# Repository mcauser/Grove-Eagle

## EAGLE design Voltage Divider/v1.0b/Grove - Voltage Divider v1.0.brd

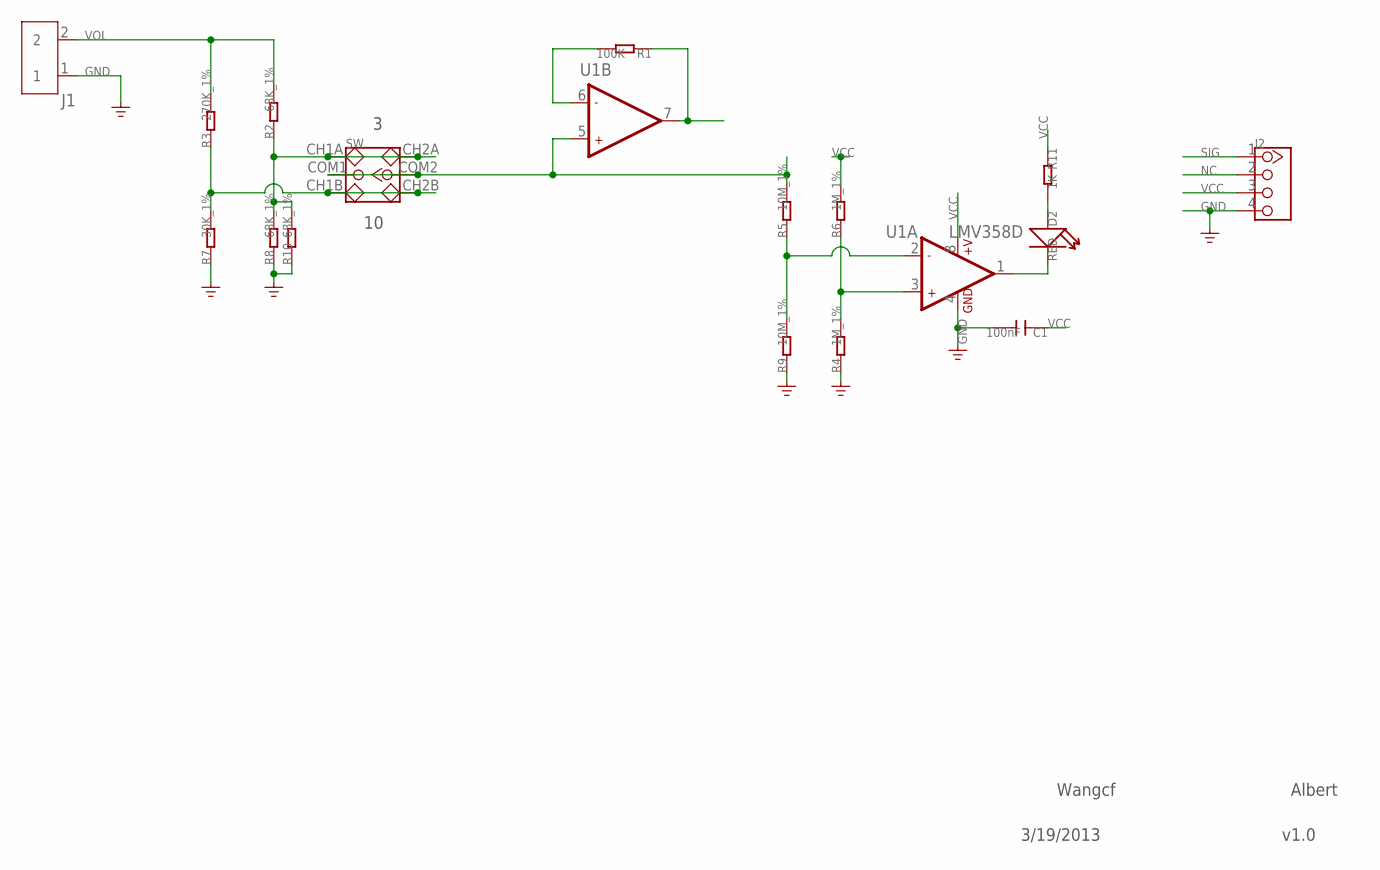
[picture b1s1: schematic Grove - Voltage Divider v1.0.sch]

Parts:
C1: 100nF; C0603
D2: RED; LED-0603
J1: SCREW-TERMINAL-2P'5.08'; 2P-5.08
J2: TWIG-4P-2.0-2.0; 4P-2.0
R1: 100K; R0603
R2, R8, R10: 68K_1%; R0603
R3: 270K_1%; R0603
R4, R6: 1M_1%; R0603
R5, R9: 10M_1%; R0603
R7: 30K_1%; R0603
R11: 1K; R0603
SW: SWITCH-2CH-6P'MS-22D18'; 6P-2CH-2.5-9.1X3.5X3.2H
U1: LMV358D; SO08

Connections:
GND: C1.2, J1.1, J2.4, R4.1, R7.1, R8.1, R9.1, R10.1, U1.4 (GND)
unnamed: D2.+, R11.2
unnamed: D2.-, U1.1 (OUT1)
unnamed: R5.1, R9.2, U1.2 (-IN1)
unnamed: R5.2, SW.COM1, SW.COM2, U1.5 (+IN2)
unnamed: R4.2, R6.1, U1.3 (+IN1)
unnamed: R1.2, U1.6 (-IN2)
NC: J2.2
SIG: J2.1, R1.1, U1.7 (OUT2)
VCC: C1.1, J2.3, R6.2, R11.1, U1.8 (+V)
VOL: J1.2, R2.2, R3.2
VOL1: R3.1, R7.2, SW.CH1B, SW.CH2B
VOL2: R2.1, R8.2, R10.2, SW.CH1A, SW.CH2A

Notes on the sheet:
Wangcf
Albert
3/19/2013
v1.0

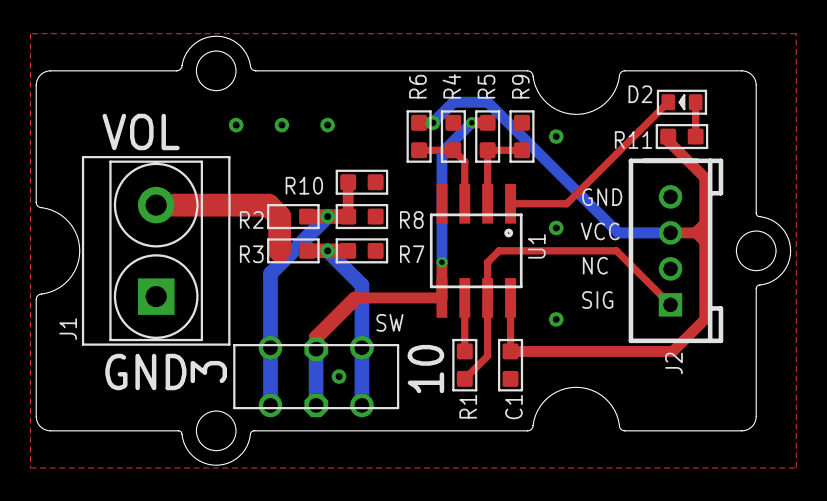
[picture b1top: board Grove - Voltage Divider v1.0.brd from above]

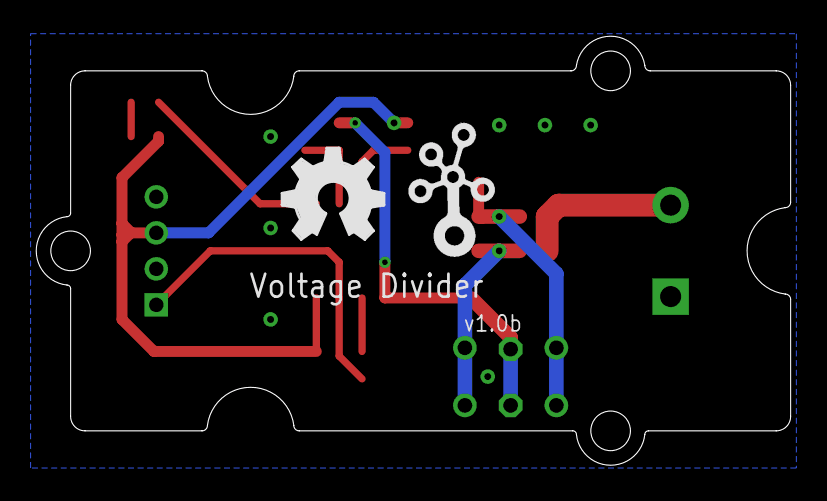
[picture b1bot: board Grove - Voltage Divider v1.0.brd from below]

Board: 2 copper layers, 41.9 x 23.8 mm, 20 parts (2 on the bottom side), 12 nets.

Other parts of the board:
U$6: 2U-DIM-W/DRILL
U$7: OSHW_FILLX200_NOTEXT
U$8: TWIGLOGO
